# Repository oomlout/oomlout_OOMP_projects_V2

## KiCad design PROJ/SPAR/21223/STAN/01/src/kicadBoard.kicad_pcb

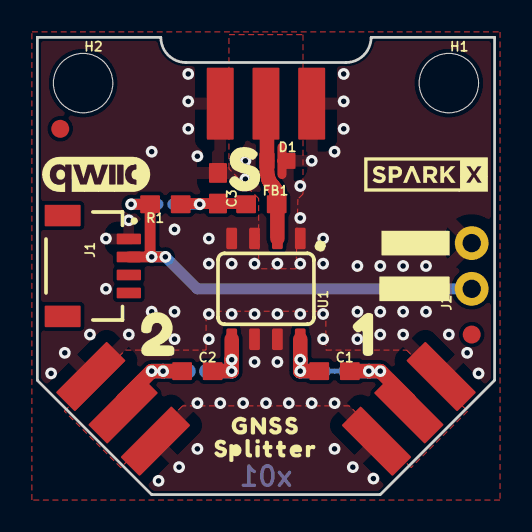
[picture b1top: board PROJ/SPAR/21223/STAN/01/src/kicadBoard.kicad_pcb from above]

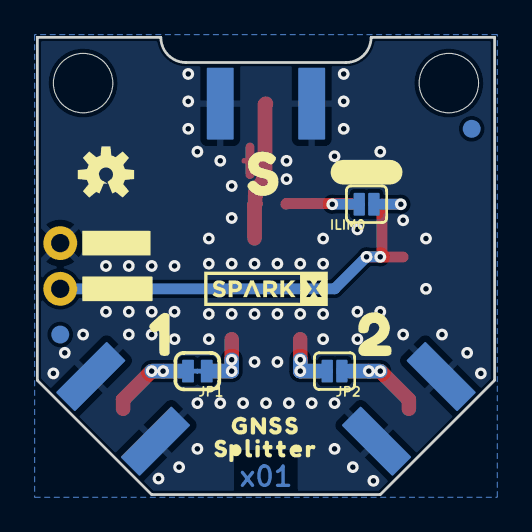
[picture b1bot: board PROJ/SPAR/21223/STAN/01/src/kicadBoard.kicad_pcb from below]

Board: 2 copper layers, 25.4 x 25.4 mm, 44 parts (16 on the bottom side), 8 nets.

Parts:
C1, C2, C3: 47pF; 0603
D1: PESD0402-0402; 0402
FB1: 30Ω/1.8A; 0603
FD1, FD2, FD3, FD4: FIDUCIAL1X2; FIDUCIAL-1X2
FRAME1: FRAME-LETTER; CREATIVE_COMMONS
H1, H2: STAND-OFF
ILIM0: JUMPER-SMT_2_NO_SILK; SMT-JUMPER_2_NO_SILK
J1: QWIIC_RIGHT_ANGLE; JST04_1MM_RA
J2: 1X02_NO_SILK
JP1: JUMPER-SMT_2_NC_TRACE_SILK; SMT-JUMPER_2_NC_TRACE_SILK
JP2: JUMPER-SMT_2_NO_SILK; SMT-JUMPER_2_NO_SILK
LOGO1: OSHW-LOGOS; OSHW-LOGO-S
LOGO2: QWIIC_LOGO_6MM; QWIIC_6MM
LOGO3: SPECIAL_INSTRUCTIONS-ORDERING; ORDERING_INSTRUCTIONS
R1: 10; 0603
S0: ANTENNA-SMA-GROUNDEDEDGE_SMA; SMA-EDGE
U1: BP2G1+_POWER_SPLITTER; XX21
U$1, U$2: SPARKX-LOGO3; SPARKX-SMALL
U$3, U$7: 10
U$4, U$8: 20
U$5, U$6: S0
U$9: #GND#0
U$10: #GND#1
U$11: #VCC#0
U$12: #VCC#1
U$13, U$16: GNSS0
U$14, U$18: P0
U$15, U$17: S__LITTER0
U$19: #ILIM#0
UNK1, UNK2: ANTENNA-SMA-GROUNDEDEDGE_SMA; SMA-EDGE

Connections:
GND: C3.1, D1.2, J1.1, J2.2, S0.GND@0, S0.GND@1, S0.GND@2, S0.GND@3, U1.1, U1.3, U1.4, U1.6, U1.7, UNK1.GND@0, UNK1.GND@1, UNK1.GND@2, UNK1.GND@3, UNK2.GND@0, UNK2.GND@1, UNK2.GND@2, UNK2.GND@3
unnamed: C1.1, JP1.1, U1.8
unnamed: C3.2, FB1.1, ILIM0.2, R1.1
unnamed: C2.2, JP2.2, U1.5
unnamed: C2.1, JP2.1, UNK2.SIG
unnamed: C1.2, JP1.2, UNK1.SIG
RF: D1.1, FB1.2, S0.SIG, U1.2
VCC: ILIM0.1, J1.2, J2.1, R1.2

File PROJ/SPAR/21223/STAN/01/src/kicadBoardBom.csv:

"Id";"Designator";"Package";"Quantity";"Designation";"Supplier and ref";
1;"D1";"0402";1;"PESD0402-0402";;;
2;"R1";"0603";1;"10";;;
3;"J2";"1X02_NO_SILK";1;"";;;
4;"U$4,U$8";"20";2;"";;;
5;"C3,C1,C2";"0603";3;"47pF";;;
6;"FD4,FD2,FD3,FD1";"FIDUCIAL-1X2";4;"FIDUCIAL1X2";;;
7;"U$13,U$16";"GNSS0";2;"";;;
8;"H1,H2";"STAND-OFF";2;"STAND-OFF";;;
9;"FRAME1";"CREATIVE_COMMONS";1;"FRAME-LETTER";;;
10;"U$1,U$2";"SPARKX-SMALL";2;"SPARKX-LOGO3";;;
11;"LOGO3";"ORDERING_INSTRUCTIONS";1;"SPECIAL_INSTRUCTIONS-ORDERING";;;
12;"LOGO2";"QWIIC_6MM";1;"QWIIC_LOGO_6MM";;;
13;"S0,UNK2,UNK1";"SMA-EDGE";3;"ANTENNA-SMA-GROUNDEDEDGE_SMA";;;
14;"U$14,U$18";"P0";2;"";;;
15;"U$9";"#GND#0";1;"";;;
16;"U1";"XX21";1;"BP2G1+_POWER_SPLITTER";;;
17;"FB1";"0603";1;"30Ω/1.8A";;;
18;"U$11";"#VCC#0";1;"";;;
19;"U$15,U$17";"S__LITTER0";2;"";;;
20;"J1";"JST04_1MM_RA";1;"QWIIC_RIGHT_ANGLE";;;
21;"U$3,U$7";"10";2;"";;;
22;"U$5,U$6";"S0";2;"";;;
23;"U$10";"#GND#1";1;"";;;
24;"U$19";"#ILIM#0";1;"";;;
25;"JP1";"SMT-JUMPER_2_NC_TRACE_SILK";1;"JUMPER-SMT_2_NC_TRACE_SILK";;;
26;"U$12";"#VCC#1";1;"";;;
27;"ILIM0,JP2";"SMT-JUMPER_2_NO_SILK";2;"JUMPER-SMT_2_NO_SILK";;;
28;"LOGO1";"OSHW-LOGO-S";1;"OSHW-LOGOS";;;

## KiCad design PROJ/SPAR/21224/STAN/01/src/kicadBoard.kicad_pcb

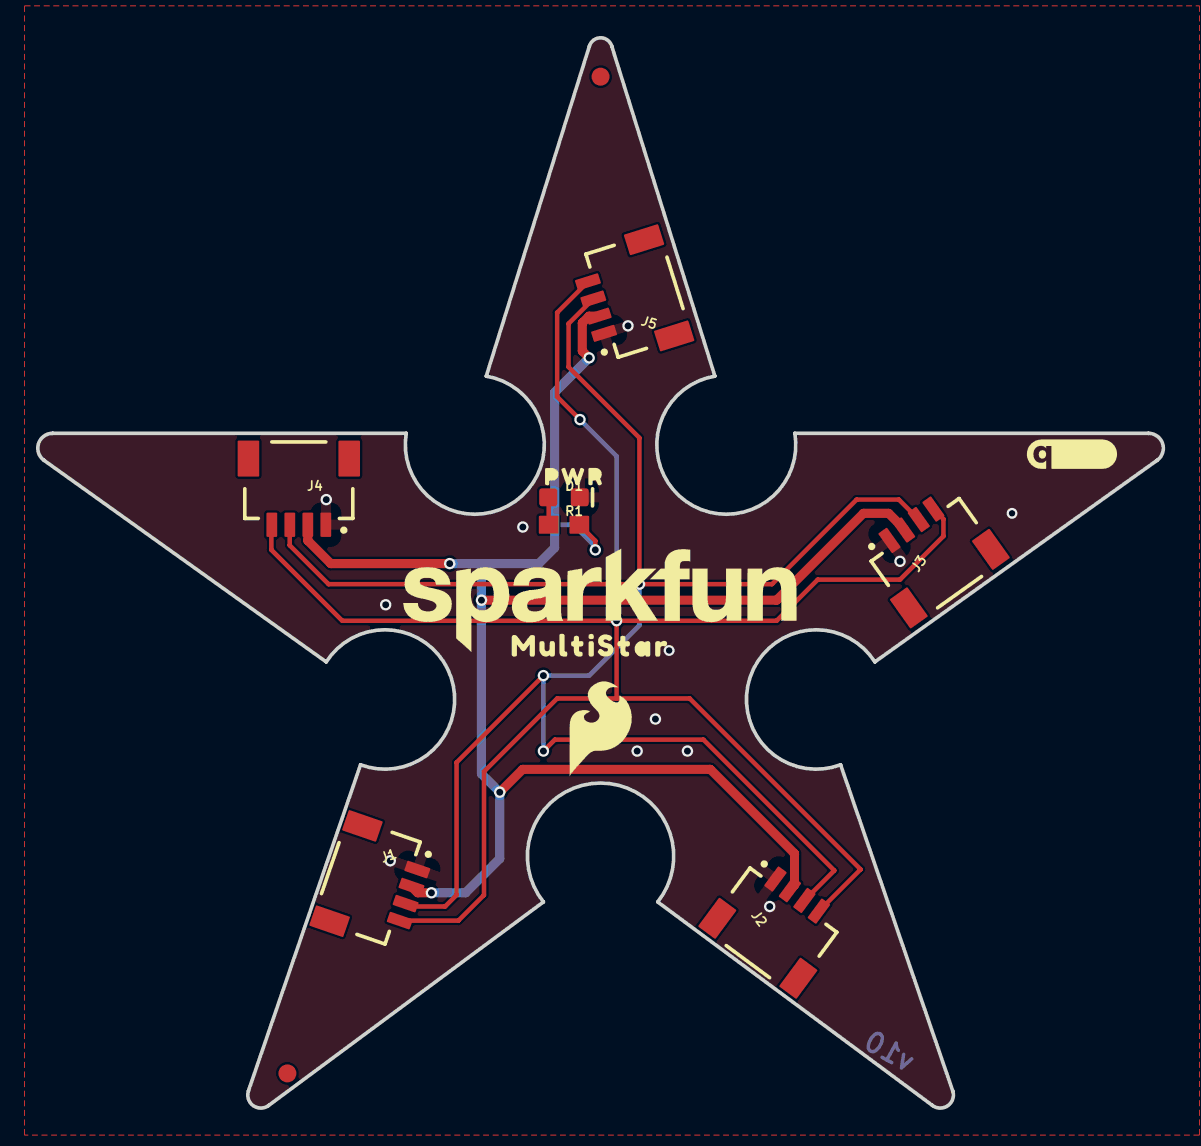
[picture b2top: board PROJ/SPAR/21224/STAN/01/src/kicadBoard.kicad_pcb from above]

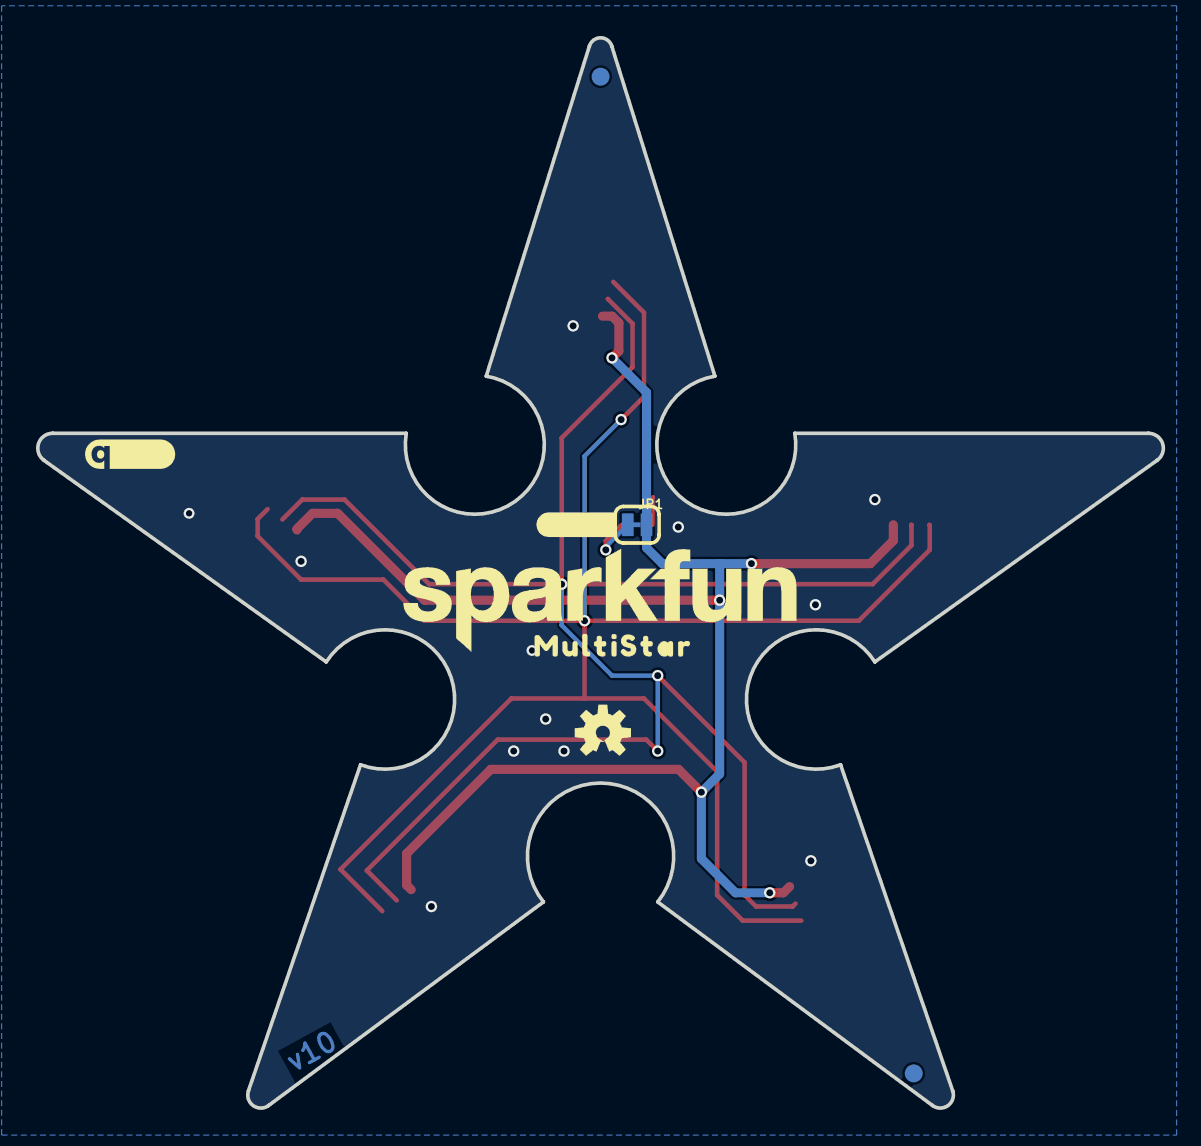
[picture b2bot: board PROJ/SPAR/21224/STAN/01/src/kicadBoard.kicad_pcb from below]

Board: 2 copper layers, 62.5 x 59.5 mm, 23 parts (8 on the bottom side), 6 nets.

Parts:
D1: RED; LED-0603
FD1, FD2, FD3, FD4: FIDUCIAL1X2; FIDUCIAL-1X2
FRAME1: FRAME-LETTER; CREATIVE_COMMONS
J1, J2, J3, J4, J5: QWIIC_RIGHT_ANGLE; JST04_1MM_RA
JP1: PWR_LED; SMT-JUMPER_2_NC_TRACE_SILK
LOGO1, LOGO2: QWIIC_LOGO_5MM; QWIIC_5MM
LOGO3: OSHW-LOGOS; OSHW-LOGO-S
LOGO4, LOGO5: SFE_LOGO_NAME.2_INCH; SFE_LOGO_NAME_.2
R1: 1k; 0603
U$2: SFE_LOGO_FLAME_.2
U$3, U$5: MULTISTAR0
U$6: #PWR#0
U$9: PWR0

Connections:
3.3V: J1.2, J2.2, J3.2, J4.2, J5.2, JP1.2
GND: D1.C, J1.1, J2.1, J3.1, J4.1, J5.1
unnamed: D1.A, R1.1
unnamed: JP1.1, R1.2
SCL: J1.4, J2.4, J3.4, J4.4, J5.4
SDA: J1.3, J2.3, J3.3, J4.3, J5.3

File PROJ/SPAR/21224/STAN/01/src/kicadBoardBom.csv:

"Id";"Designator";"Package";"Quantity";"Designation";"Supplier and ref";
1;"J3,J2,J5,J4,J1";"JST04_1MM_RA";5;"QWIIC_RIGHT_ANGLE";;;
2;"LOGO5,LOGO4";"SFE_LOGO_NAME_.2";2;"SFE_LOGO_NAME.2_INCH";;;
3;"LOGO2,LOGO1";"QWIIC_5MM";2;"QWIIC_LOGO_5MM";;;
4;"R1";"0603";1;"1k";;;
5;"FD3,FD1,FD4,FD2";"FIDUCIAL-1X2";4;"FIDUCIAL1X2";;;
6;"U$3,U$5";"MULTISTAR0";2;"";;;
7;"D1";"LED-0603";1;"RED";;;
8;"U$9";"PWR0";1;"";;;
9;"U$2";"SFE_LOGO_FLAME_.2";1;"";;;
10;"FRAME1";"CREATIVE_COMMONS";1;"FRAME-LETTER";;;
11;"U$6";"#PWR#0";1;"";;;
12;"JP1";"SMT-JUMPER_2_NC_TRACE_SILK";1;"PWR_LED";;;
13;"LOGO3";"OSHW-LOGO-S";1;"OSHW-LOGOS";;;

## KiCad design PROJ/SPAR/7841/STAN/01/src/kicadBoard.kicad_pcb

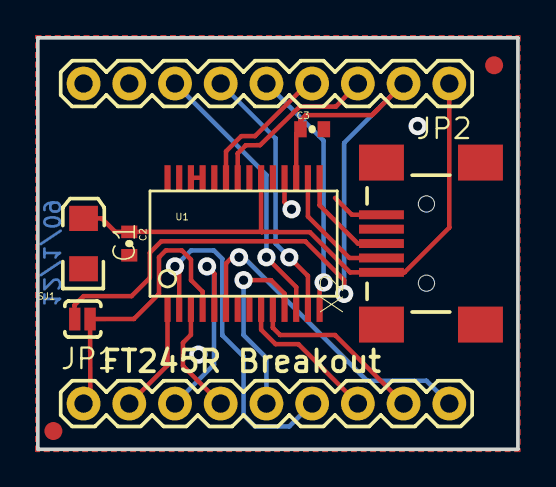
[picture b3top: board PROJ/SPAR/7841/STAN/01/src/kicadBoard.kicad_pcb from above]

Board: 2 copper layers, 26.7 x 22.9 mm, 11 parts (1 on the bottom side), 19 nets.

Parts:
C1: 10uF; CPOL_1206
C2, C3: 0.1uF; 0402-CAP
JP1, JP2: M09; 1X09
JP3, JP4: FIDUCIAL1X2; FIDUCIAL-1X2
SJ1: SOLDERJUMPERNC2; SJ_2S-NOTRACE
U1: FT245RL; SSOP28DB
U$1: LOGO-SFENEW; SFE-NEW-WEBLOGO
X2: USBSMD; USB-MINIB

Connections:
3.3V: C3.1, JP2.2, SJ1.1, U1.17
D0: JP1.2, U1.1
D1: JP1.3, U1.5
D2: JP1.4, U1.3
D3: JP1.5, U1.11
D4: JP1.6, U1.2
D5: JP1.7, U1.9
D6: JP1.8, U1.10
D7: JP1.9, U1.6
GND: C1.C, C2.2, C3.2, JP2.8, JP2.9, U1.7, U1.18, U1.21, U1.25, U1.26, X2.GND
PWEN: JP2.7, U1.12
RD: JP2.6, U1.13
RXF: JP2.4, U1.23
TXE: JP2.3, U1.22
USB_D+: U1.15, X2.D+
USB_D-: U1.16, X2.D-
VCCIO: JP1.1, SJ1.2, U1.4
VUSB: C1.A, C2.1, JP2.1, U1.20, X2.VBUS
WR: JP2.5, U1.14

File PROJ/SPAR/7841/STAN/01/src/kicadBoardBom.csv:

"Id";"Designator";"Package";"Quantity";"Designation";"Supplier and ref";
1;"JP3,JP4";"FIDUCIAL-1X2";2;"FIDUCIAL1X2";;;
2;"JP1,JP2";"1X09";2;"M09";;;
3;"SJ1";"SJ_2S-NOTRACE";1;"SOLDERJUMPERNC2";;;
4;"C3,C2";"0402-CAP";2;"0.1uF";;;
5;"X2";"USB-MINIB";1;"USBSMD";;;
6;"U1";"SSOP28DB";1;"FT245RL";;;
7;"C1";"CPOL_1206";1;"10uF";;;
8;"U$1";"SFE-NEW-WEBLOGO";1;"LOGO-SFENEW";;;

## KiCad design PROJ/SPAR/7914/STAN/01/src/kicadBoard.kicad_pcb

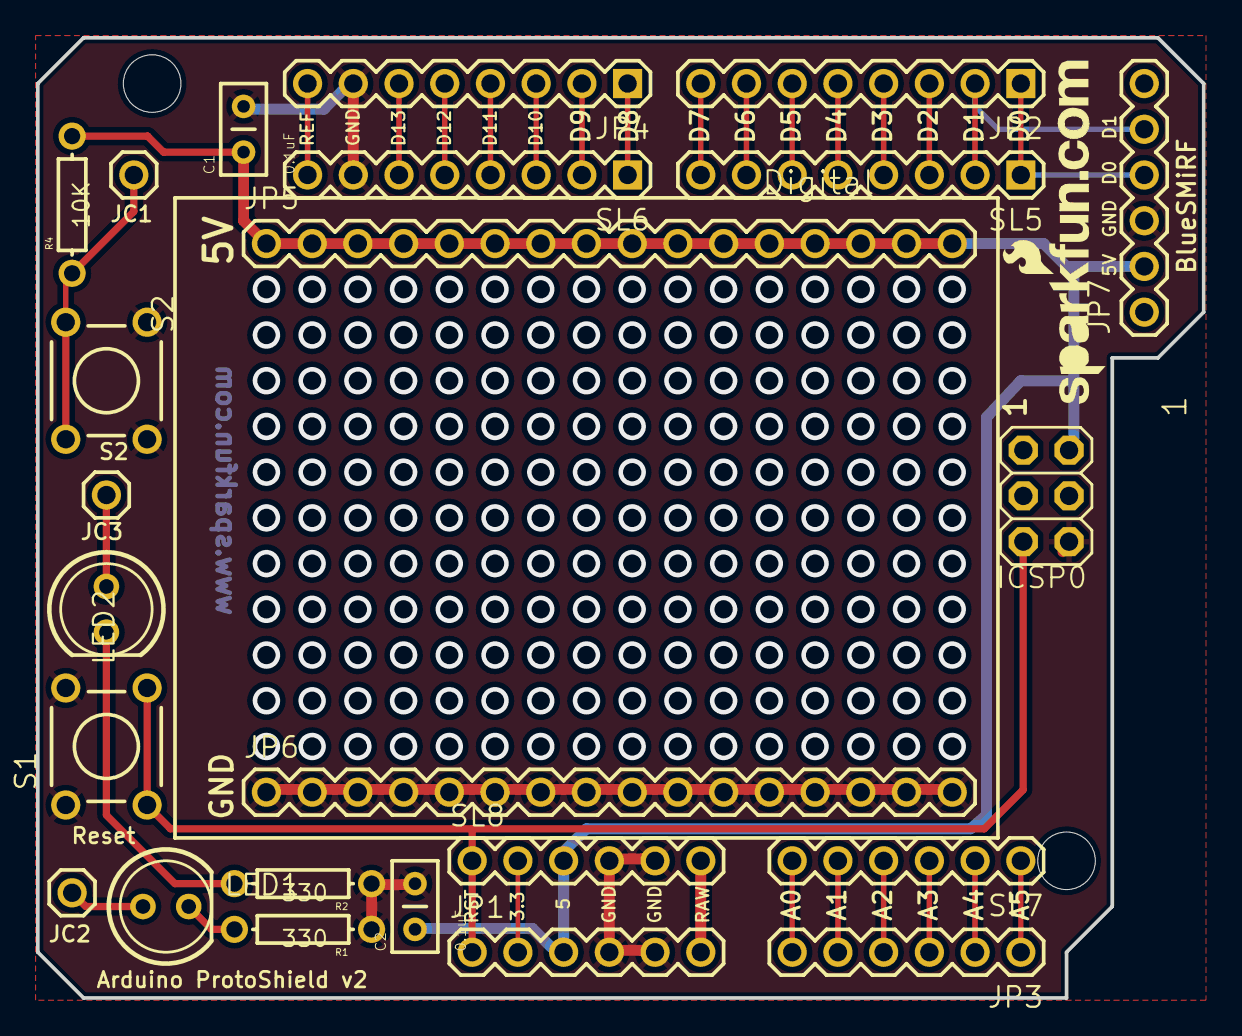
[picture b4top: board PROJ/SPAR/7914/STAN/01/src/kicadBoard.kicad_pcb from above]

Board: 2 copper layers, 64.8 x 53.3 mm, 29 parts (0 on the bottom side), 31 nets.

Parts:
@HOLE0, @HOLE1: (no value)
BB1: BREADBOARDMINI; BREADBOARD-MINI
C1, C2: 0.1uF; CAP-PTH-SMALL2
ICSP0: ICSP; 2X03
JC1, JC2, JC3: M01PTH; 1X01
JP1: Power; 1X06
JP2: Digital1; 1X08
JP3: Analog; 1X06
JP4: Digital2; 1X08
JP5, JP6: M16PTH; 1X16
JP7: BlueSMiRF; 1X06
LED1, LED2: LED5MM
R1, R2: 330; AXIAL-0.3
R4: 10K; AXIAL-0.3
S1: Reset; TACTILE-PTH
S2: TACTILE-PTH
SL5, SL6: 1X08
SL7, SL8: 1X06
U$1: LOGO-SFENEW; SFE-NEW-WEBLOGO
U$2: CREATIVE_COMMONS

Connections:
3.3V: JP1.2, SL8.2
5V: C1.1, C2.1, ICSP0.2, JP1.3, JP5.1, JP5.2, JP5.3, JP5.4, JP5.5, JP5.6, JP5.7, JP5.8, JP5.9, JP5.10, JP5.11, JP5.12, JP5.13, JP5.14, JP5.15, JP5.16, JP7.2, R4.P$2, SL8.3
A0: JP3.6, SL7.6
A1: JP3.5, SL7.5
A2: JP3.4, SL7.4
A3: JP3.3, SL7.3
A4: JP3.2, SL7.2
A5: JP3.1, SL7.1
AREF: JP4.8, SL6.8
D2: JP2.3, SL5.3
D3: JP2.4, SL5.4
D4: JP2.5, SL5.5
D5: JP2.6, SL5.6
D6: JP2.7, SL5.7
D7: JP2.8, SL5.8
D8: JP4.1, SL6.1
D9: JP4.2, SL6.2
D10: JP4.3, SL6.3
D11: JP4.4, SL6.4
D12: JP4.5, SL6.5
D13: JP4.6, SL6.6
GND: C1.2, C2.2, ICSP0.6, JP1.4, JP1.5, JP4.7, JP6.1, JP6.2, JP6.3, JP6.4, JP6.5, JP6.6, JP6.7, JP6.8, JP6.9, JP6.10, JP6.11, JP6.12, JP6.13, JP6.14, JP6.15, JP6.16, JP7.3, R1.P$1, R2.P$1, S1.1, S1.2, S2.1, S2.2, SL6.7, SL8.4, SL8.5
LED1: JC2.1, LED1.A
LED2: JC3.1, LED2.A
unnamed: LED1.K, R1.P$2
unnamed: LED2.K, R2.P$2
RES: JC1.1, R4.P$1, S2.3, S2.4
RESET: ICSP0.5, JP1.1, S1.3, S1.4, SL8.1
RX: JP2.1, JP7.4, SL5.1
TX: JP2.2, JP7.5, SL5.2
VIN: JP1.6, SL8.6

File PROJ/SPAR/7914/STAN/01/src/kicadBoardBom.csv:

"Id";"Designator";"Package";"Quantity";"Designation";"Supplier and ref";
1;"S2";"TACTILE-PTH";1;"";;;
2;"S1";"TACTILE-PTH";1;"Reset";;;
3;"R4";"AXIAL-0.3";1;"10K";;;
4;"LED1,LED2";"LED5MM";2;"";;;
5;"JC2,JC3,JC1";"1X01";3;"M01PTH";;;
6;"JP5,JP6";"1X16";2;"M16PTH";;;
7;"R2,R1";"AXIAL-0.3";2;"330";;;
8;"C2,C1";"CAP-PTH-SMALL2";2;"0.1uF";;;
9;"JP1";"1X06";1;"Power";;;
10;"SL7,SL8";"1X06";2;"";;;
11;"JP2";"1X08";1;"Digital1";;;
12;"@HOLE1,@HOLE0";"";2;"";;;
13;"JP7";"1X06";1;"BlueSMiRF";;;
14;"JP3";"1X06";1;"Analog";;;
15;"U$2";"CREATIVE_COMMONS";1;"CREATIVE_COMMONS";;;
16;"ICSP0";"2X03";1;"ICSP";;;
17;"U$1";"SFE-NEW-WEBLOGO";1;"LOGO-SFENEW";;;
18;"BB1";"BREADBOARD-MINI";1;"BREADBOARDMINI";;;
19;"SL5,SL6";"1X08";2;"";;;
20;"JP4";"1X08";1;"Digital2";;;

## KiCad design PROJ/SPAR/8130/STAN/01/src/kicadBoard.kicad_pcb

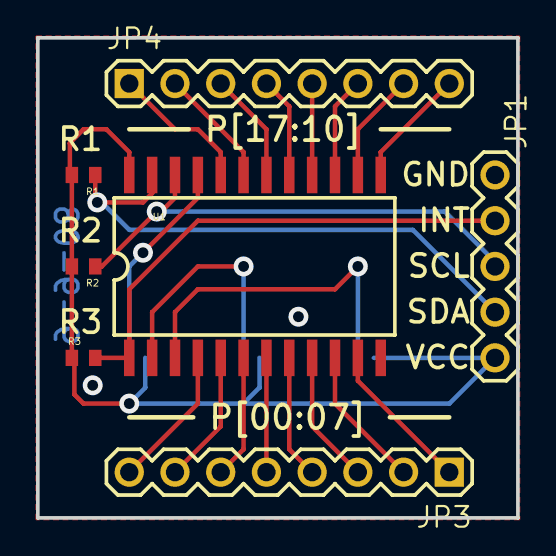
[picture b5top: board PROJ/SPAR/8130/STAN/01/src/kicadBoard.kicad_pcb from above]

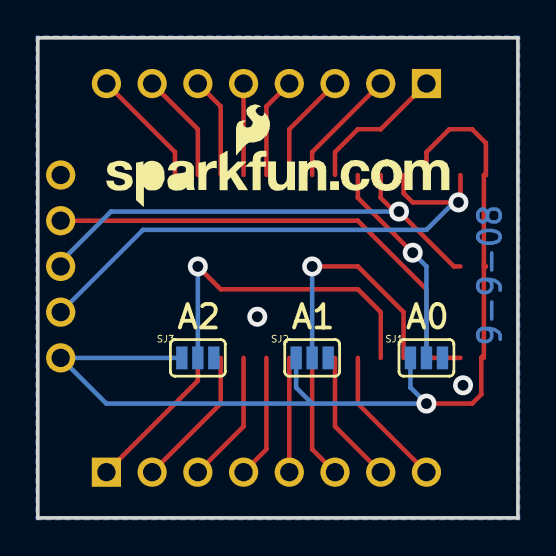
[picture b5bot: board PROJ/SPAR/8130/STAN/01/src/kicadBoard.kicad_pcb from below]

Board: 2 copper layers, 26.7 x 26.7 mm, 11 parts (4 on the bottom side), 24 nets.

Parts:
JP1: 1X05
JP3, JP4: 1X08
R1, R2, R3: C0402
SJ1: A0; SJ_3
SJ2: A1; SJ_3
SJ3: A2; SJ_3
U1: PCF8575C; SO-24DW
U$2: LOGO-SFENEW; SFE-NEW-WEBLOGO

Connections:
A0: SJ1.2, U1.21
A1: SJ2.2, U1.2
A2: SJ3.2, U1.3
GND: JP1.1, SJ1.3, SJ2.3, SJ3.3, U1.12
INT: JP1.2, R3.2, U1.1
P10: JP4.8, U1.13
P11: JP4.7, U1.14
P12: JP4.6, U1.15
P13: JP4.5, U1.16
P14: JP4.4, U1.17
P15: JP4.3, U1.18
P16: JP4.2, U1.19
P17: JP4.1, U1.20
PO0: JP3.8, U1.4
PO1: JP3.7, U1.5
PO2: JP3.6, U1.6
PO3: JP3.5, U1.7
PO4: JP3.4, U1.8
PO5: JP3.3, U1.9
PO6: JP3.2, U1.10
PO7: JP3.1, U1.11
SCL: JP1.3, R2.1, U1.22
SDA: JP1.4, R1.1, U1.23
VCC: JP1.5, R1.2, R2.2, R3.1, SJ1.1, SJ2.1, SJ3.1, U1.24

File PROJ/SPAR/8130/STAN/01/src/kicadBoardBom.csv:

"Id";"Designator";"Package";"Quantity";"Designation";"Supplier and ref";
1;"JP4,JP3";"1X08";2;"";;;
2;"R1,R2,R3";"C0402";3;"";;;
3;"U1";"SO-24DW";1;"PCF8575C";;;
4;"JP1";"1X05";1;"";;;
5;"SJ3";"SJ_3";1;"A2";;;
6;"SJ2";"SJ_3";1;"A1";;;
7;"U$2";"SFE-NEW-WEBLOGO";1;"LOGO-SFENEW";;;
8;"SJ1";"SJ_3";1;"A0";;;

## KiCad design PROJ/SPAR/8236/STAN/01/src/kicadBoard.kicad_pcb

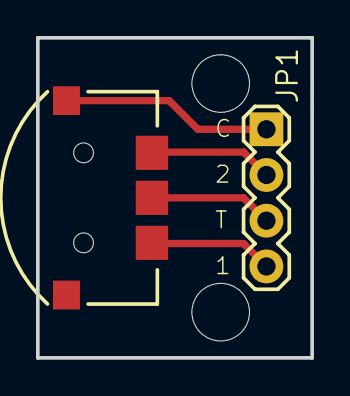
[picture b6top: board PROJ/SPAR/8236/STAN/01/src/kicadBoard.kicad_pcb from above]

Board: 2 copper layers, 15.2 x 17.8 mm, 5 parts (1 on the bottom side), 4 nets.

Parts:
@HOLE0, @HOLE1: (no value)
JP1: 1X04
JP2: NAV_SWITCH
U$1: LOGO-SFESK; SFE-LOGO-FLAME

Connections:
unnamed: JP1.1, JP2.C
unnamed: JP1.2, JP2.2
unnamed: JP1.3, JP2.T
unnamed: JP1.4, JP2.1

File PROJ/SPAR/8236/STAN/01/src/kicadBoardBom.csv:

"Id";"Designator";"Package";"Quantity";"Designation";"Supplier and ref";
1;"@HOLE0,@HOLE1";"";2;"";;;
2;"JP2";"NAV_SWITCH";1;"NAV_SWITCH";;;
3;"JP1";"1X04";1;"";;;
4;"U$1";"SFE-LOGO-FLAME";1;"LOGO-SFESK";;;

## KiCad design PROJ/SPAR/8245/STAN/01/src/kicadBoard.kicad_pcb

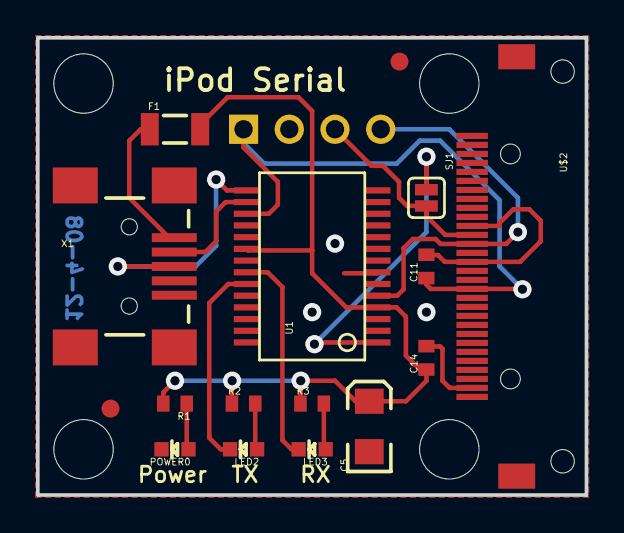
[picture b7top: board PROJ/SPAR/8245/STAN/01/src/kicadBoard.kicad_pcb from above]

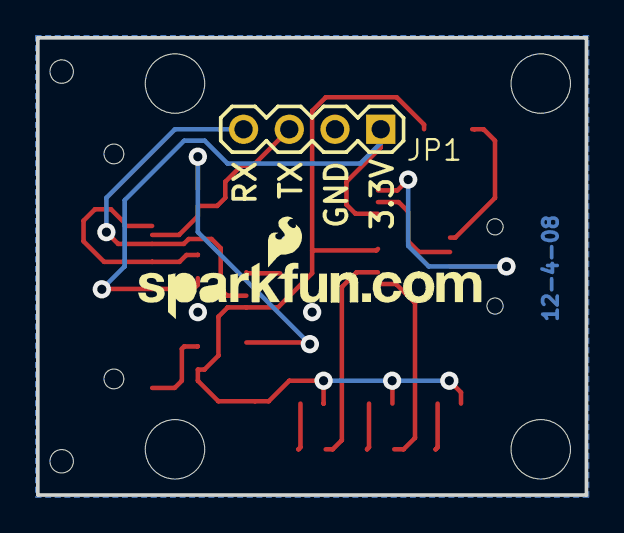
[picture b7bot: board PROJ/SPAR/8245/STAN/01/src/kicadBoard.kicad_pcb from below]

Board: 2 copper layers, 30.5 x 25.4 mm, 23 parts (2 on the bottom side), 14 nets.

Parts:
C5: 10uF; EIA3216
C11, C14: 0.1uF; C0402
F1: 500mA-PTC; PTC-1206
JP1: 1X04
LED2: Red; LED-0603
LED3: Green; LED-0603
POWER0: Red; LED-0603
R1: 330; C0402
R2, R3: 1K; C0402
SJ1: SOLDERJUMPERNC2; SJ_2S
U1: FT232RL-BASICSSOP; SSOP28DB
U$1, U$5, U$6, U$7: STAND-OFF
U$2: IPOD_CONNECTOR_FEMALE; IPOD_FEMALE_CONNECTOR
U$3: LOGO-SFENEW; SFE-NEW-WEBLOGO
U$4, U$8: FIDUCIAL1X2; FIDUCIAL-1X2
U$9: CREATIVE_COMMONS
X1: USBSMD; USB-MINIB

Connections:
3.3V: C11.1, JP1.1, U1.17, U$2.18
5V: C5.A, C14.1, F1.2, R1.2, R2.1, R3.1, U1.4, U1.20
GND: C5.C, C11.2, C14.2, JP1.2, POWER0.C, U1.7, U1.18, U1.21, U1.25, U1.26, U$2.1, U$2.11, U$2.15, U$2.16, U$2.29, U$2.30, X1.GND
unnamed: POWER0.A, R1.1
unnamed: U1.15, X1.D+
unnamed: LED2.A, R2.2
unnamed: LED3.A, R3.2
unnamed: U1.16, X1.D-
RXLED: LED3.C, U1.22
TXD: JP1.3, SJ1.2, U$2.12
TXLED: LED2.C, U1.23
USB-RX: JP1.4, U1.5, U$2.13
USB-TX: SJ1.1, U1.1
USBVCC: F1.1, X1.VBUS

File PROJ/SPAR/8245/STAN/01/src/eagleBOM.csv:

"Part";"Value";"Device";"Package";"Description";"";
"C5";"10uF";"CAP_POL1206";"EIA3216";"Capacitor Polarized";"";
"C11";"0.1uF";"CAP0402";"C0402";"Capacitor";"";
"C14";"0.1uF";"CAP0402";"C0402";"Capacitor";"";
"F1";"500mA-PTC";"PTCSMD";"PTC-1206";"Resettable Fuse PTC";"";
"JP1";"";"M04PTH";"1X04";"Header 4";"";
"LED2";"Red";"LED0603";"LED-0603";"LEDs";"";
"LED3";"Green";"LED0603";"LED-0603";"LEDs";"";
"POWER";"Red";"LED0603";"LED-0603";"LEDs";"";
"R1";"330";"RESISTOR0402";"C0402";"Resistor";"";
"R2";"1K";"RESISTOR0402";"C0402";"Resistor";"";
"R3";"1K";"RESISTOR0402";"C0402";"Resistor";"";
"SJ1";"SOLDERJUMPERNC2";"SOLDERJUMPERNC2";"SJ_2S";"Solder Jumper";"";
"U$1";"STAND-OFF";"STAND-OFF";"STAND-OFF";"Stand Off";"";
"U$2";"IPOD_CONNECTOR_FEMALE";"IPOD_CONNECTOR_FEMALE";"IPOD_FEMALE_CONNECTOR";"iPod Female Connector";"";
"U$3";"LOGO-SFENEW";"LOGO-SFENEW";"SFE-NEW-WEBLOGO";"Spark Fun Electronics PCB Logo";"";
"U$4";"FIDUCIAL1X2";"FIDUCIAL1X2";"FIDUCIAL-1X2";"Fiducial Alignment Points";"";
"U$5";"STAND-OFF";"STAND-OFF";"STAND-OFF";"Stand Off";"";
"U$6";"STAND-OFF";"STAND-OFF";"STAND-OFF";"Stand Off";"";
"U$7";"STAND-OFF";"STAND-OFF";"STAND-OFF";"Stand Off";"";
"U$8";"FIDUCIAL1X2";"FIDUCIAL1X2";"FIDUCIAL-1X2";"Fiducial Alignment Points";"";
"U$9";"CREATIVE_COMMONS";"CREATIVE_COMMONS";"CREATIVE_COMMONS";"";"";
"U1";"FT232RL-BASICSSOP";"FT232RL-BASICSSOP";"SSOP28DB";"USB UART";"";
"X1";"USBSMD";"USBSMD";"USB-MINIB";"USB Connectors";"";

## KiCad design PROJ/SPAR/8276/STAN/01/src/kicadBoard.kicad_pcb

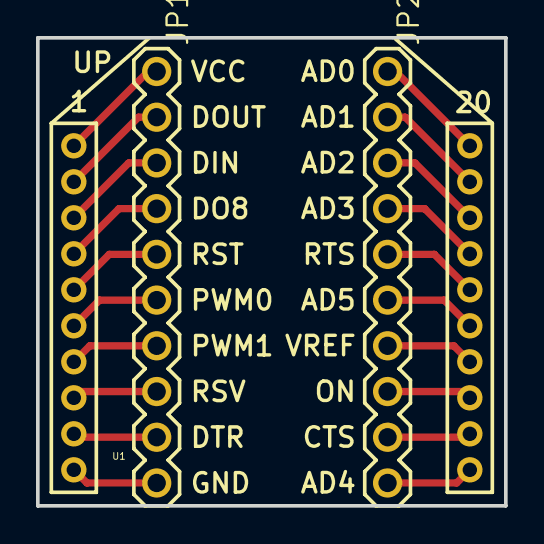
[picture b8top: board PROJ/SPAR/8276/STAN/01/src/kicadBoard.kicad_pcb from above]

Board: 2 copper layers, 26.0 x 26.0 mm, 4 parts (1 on the bottom side), 20 nets.

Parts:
JP1, JP2: 1X10
U1: XBEE; XBEE-1
U$2: LOGO-SFENEW; SFE-NEW-WEBLOGO

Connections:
unnamed: JP1.5, U1.5
unnamed: JP1.1, U1.1
unnamed: JP1.2, U1.2
unnamed: JP1.3, U1.3
unnamed: JP1.4, U1.4
unnamed: JP1.6, U1.6
unnamed: JP1.7, U1.7
unnamed: JP1.8, U1.8
unnamed: JP1.9, U1.9
unnamed: JP1.10, U1.10
unnamed: JP2.10, U1.11
unnamed: JP2.9, U1.12
unnamed: JP2.8, U1.13
unnamed: JP2.7, U1.14
unnamed: JP2.6, U1.15
unnamed: JP2.5, U1.16
unnamed: JP2.4, U1.17
unnamed: JP2.3, U1.18
unnamed: JP2.2, U1.19
unnamed: JP2.1, U1.20

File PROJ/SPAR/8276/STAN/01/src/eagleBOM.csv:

"Part";"Value";"Device";"Package";"Description";"";
"JP1";"";"M100.1";"1X10";"Header 10";"";
"JP2";"";"M100.1";"1X10";"Header 10";"";
"U$2";"LOGO-SFENEW";"LOGO-SFENEW";"SFE-NEW-WEBLOGO";"Spark Fun Electronics PCB Logo";"";
"U1";"XBEE";"XBEE-1B1";"XBEE-1";"";"";

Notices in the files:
parts and their libraries:
RELEASED UNDER THE CREATIVE COMMONS ATTRIBUTION SHARE-ALIKE 4.0 LICENSE
HTTPS://CREATIVECOMMONS.ORG/LICENSES/BY-SA/4.0
RELEASED UNDER THE CREATIVE COMMONS ATTRIBUTION SHARE-ALIKE 3.0 LICENSE
HTTP://CREATIVECOMMONS.ORG/LICENSES/BY-SA/3.0
